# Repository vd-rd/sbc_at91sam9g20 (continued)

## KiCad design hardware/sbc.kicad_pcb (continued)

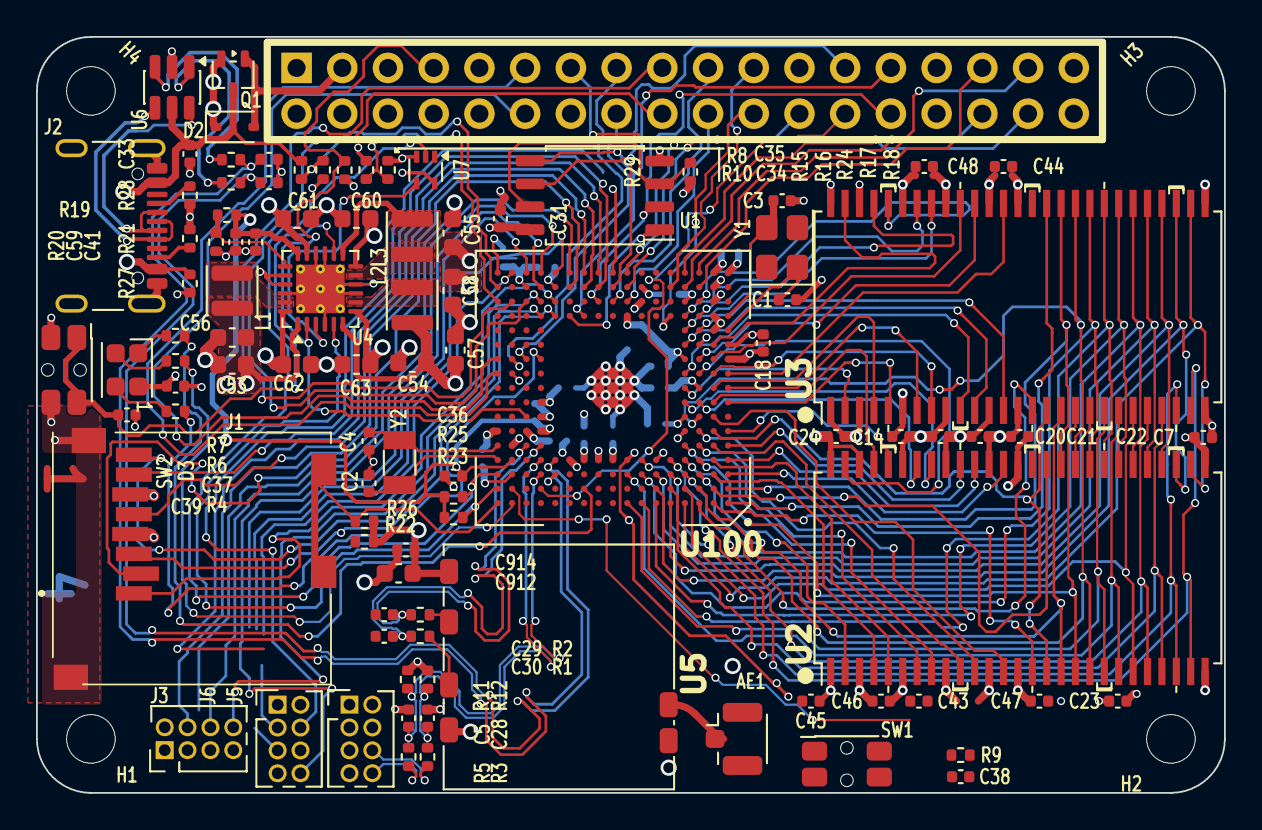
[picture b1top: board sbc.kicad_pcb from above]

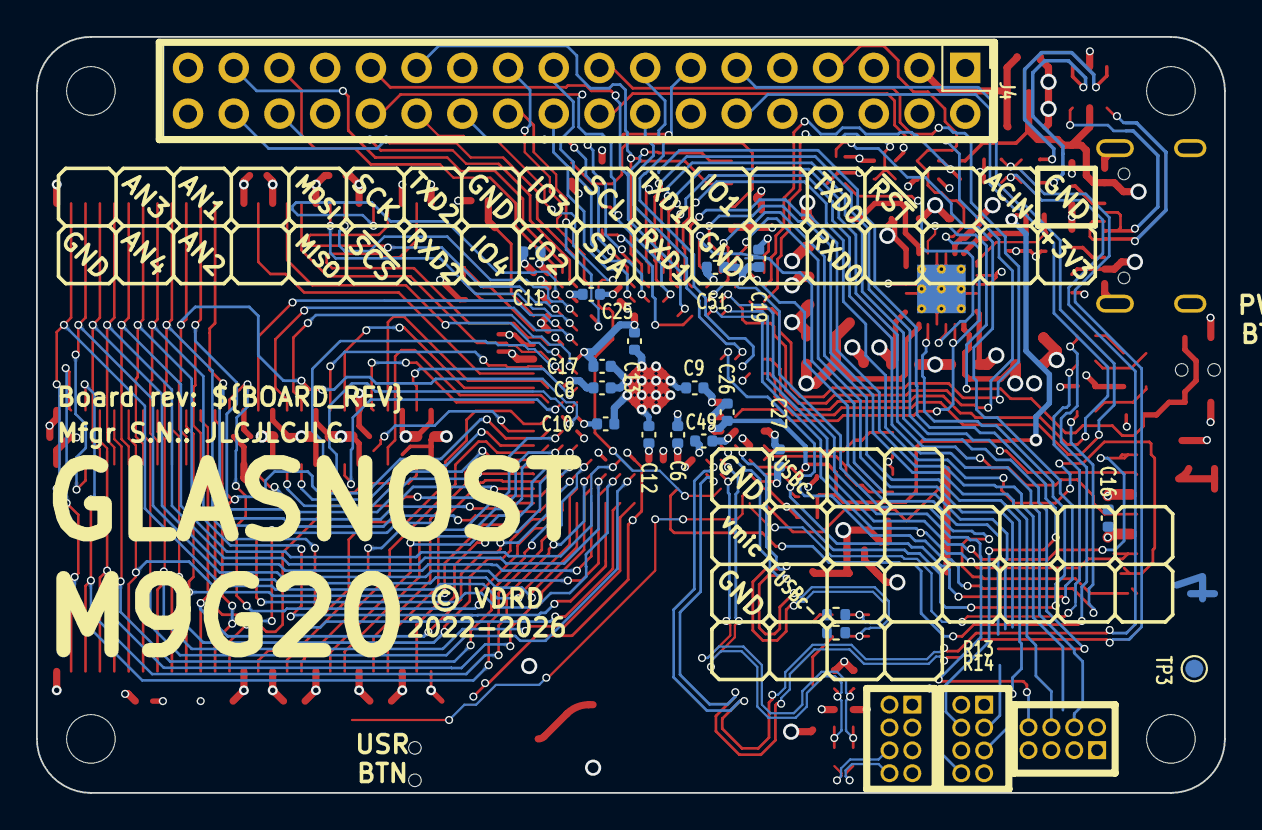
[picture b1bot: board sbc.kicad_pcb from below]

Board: 4 copper layers, 66.0 x 42.0 mm, 118 parts (19 on the bottom side), 143 nets.

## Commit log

2019-05-10 project: structure bringup
2019-05-13 board: defined floorplan
2019-05-13 layout: added bga sdram variant
2021-02-24 design: sdram connections defined
2021-11-30 kicad bringup
2021-12-05 added decoupling caps
2021-12-07 define cpu nets
2021-12-08 small fixes
2021-12-13 more sdram routing
2022-01-03 add preliminary board render
2022-01-04 rearranged components
2022-01-13 added nor flash
2022-01-14 repositioned components on board, added nor storage
2022-01-16 add layer identification labels
2022-02-21 small ddr fixes
2022-03-09 fix usb connector
2022-03-24 fix project structure
2022-03-30 fix sdram wire width
2022-04-05 finish sdram
2022-04-05 small changes
2022-04-07 swap pmic for mcp16501
2022-04-07 upload new board preview
2022-04-07 add power rails
2022-04-07 add silk info
2022-04-15 fix spi bus
2022-05-03 add bga parts
2022-05-14 add usb esd
2022-05-15 more routing for rmii
2022-05-15 add nand flash
2022-05-22 fix eth header for compatibility
2022-05-28 route rmii bus
2022-05-28 define usb connector
2022-05-29 move bulk caps to input zone
2022-05-29 fixed wrong pullup on SDIO bus
2022-06-16 new routing work
2022-06-29 update project
2022-07-11 prepare for fab release
2022-11-22 update schematic on par with normal sdram
2024-05-13 bump format to kicad 8
2024-05-21 bump to kicad 8
2024-08-05 updated silkscreen labels
2024-08-05 remove extra files
2024-10-28 added tps and cleaned silk
2025-03-18 rework power delivery
2025-03-18 reorg project structure
2025-07-25 added rounded tracks
2026-01-26 backport changes from other boards
2026-01-26 updated board layout and project structure
2026-02-02 backport features
2026-02-03 modified pmic layout
2026-02-03 more routing
2026-04-30 almost done for rev 2
2026-05-02 updated gitignore
2026-05-23 small routing for v2
2026-05-23 cosmetics for rev2
2026-05-25 fix drc for rev2
